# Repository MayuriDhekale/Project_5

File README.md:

# Project_5
<br>
<b>STM32F411 Multi Sensor Dashboard</b>
<br>
Moving beyond previous concepts, i have engineered this platform from clean sheet schematic to a dense, 4 layer routing solution. This custom 4-layer PCB was engineered to isolate high-frequency digital noise from the 100MHz STM32 processor, protecting the delicate micro-volt data of the MPU6050 and BMP280 sensors.

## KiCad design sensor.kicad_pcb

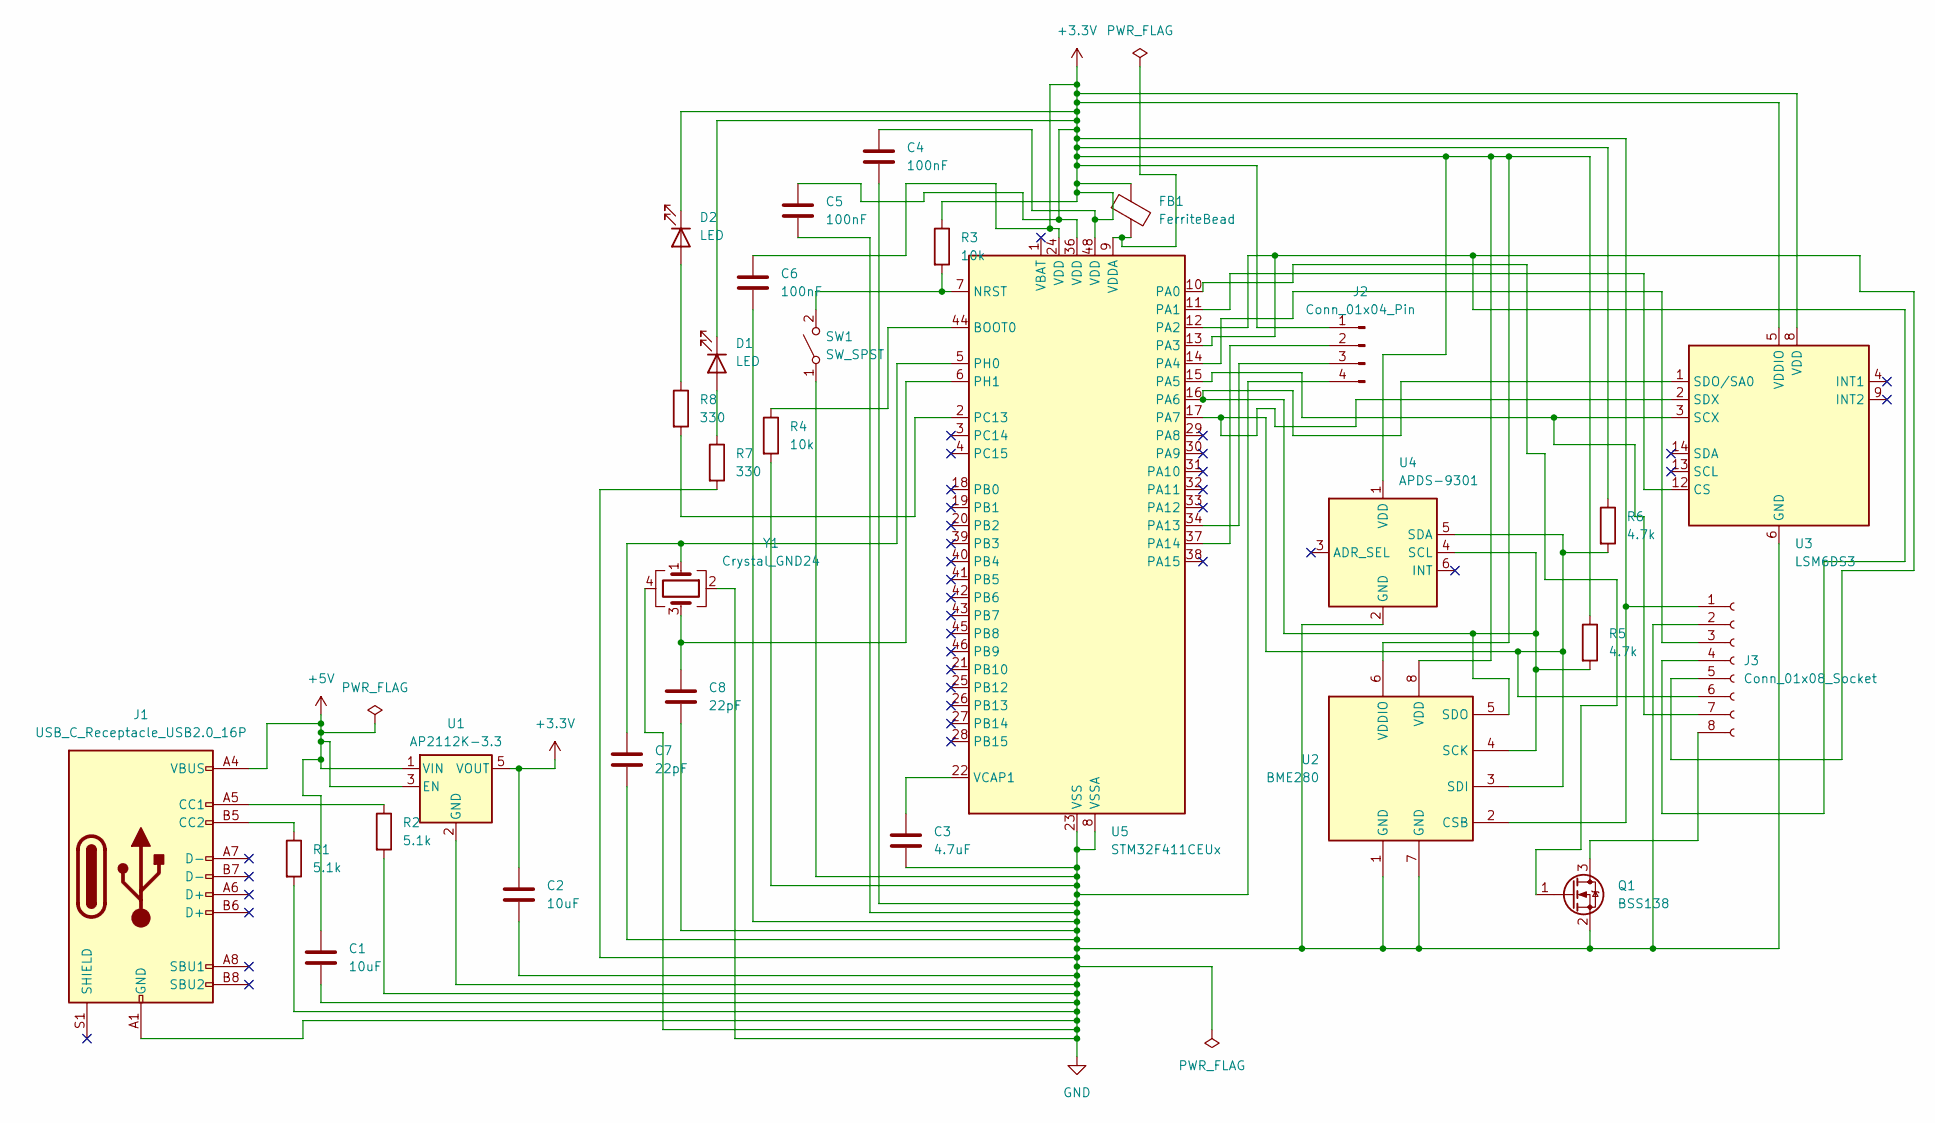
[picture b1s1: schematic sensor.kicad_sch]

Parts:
C1, C2: 10uF; C_0805_2012Metric
C3: 4.7uF; C_0603_1608Metric
C4, C5, C6: 100nF; C_0603_1608Metric
C7, C8: 22pF; C_0603_1608Metric
D1, D2: LED; LED_D5.0mm
FB1: FerriteBead; L_0603_1608Metric
J1: USB_C_Receptacle_USB2.0_16P; USB_C_Receptacle_HRO_TYPE-C-31-M-12
J2: Conn_01x04_Pin; PinHeader_1x04_P2.54mm_Vertical
J3: Conn_01x08_Socket; PinHeader_1x08_P2.54mm_Vertical
Q1: BSS138; SOT-23
R1, R2: 5.1k; R_0603_1608Metric
R3, R4: 10k; R_0603_1608Metric
R5, R6: 4.7k; R_0603_1608Metric
R7, R8: 330; R_0603_1608Metric
SW1: SW_SPST; SW_SPST_PTS645
U1: AP2112K-3.3; SOT-23-5
U2: BME280; Bosch_LGA-8_2.5x2.5mm_P0.65mm_ClockwisePinNumbering
U3: LSM6DS3; LGA-14_3x2.5mm_P0.5mm_LayoutBorder3x4y
U4: APDS-9301; Broadcom_APDS-9301
U5: STM32F411CEUx; QFN-48-1EP_7x7mm_P0.5mm_EP5.6x5.6mm
Y1: Crystal_GND24; Crystal_SMD_3225-4Pin_3.2x2.5mm

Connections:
+3.3V: C2.1, C4.1, C5.1, C6.1, D1.1 (K), D2.1 (K), FB1.1, J2.1, J3.1, R3.1, R5.1, R6.1, U1.5 (VOUT), U2.2 (CSB), U2.6 (VDDIO), U2.8 (VDD), U3.5 (VDDIO), U3.8 (VDD), U4.1 (VDD), U5.24 (VDD), U5.36 (VDD), U5.48 (VDD)
+5V: C1.1, J1.A4 (VBUS), J1.A9 (VBUS), J1.B4 (VBUS), J1.B9 (VBUS), U1.1 (VIN), U1.3 (EN)
GND: C1.2, C2.2, C3.2, C4.2, C5.2, C6.2, C7.2, C8.2, J1.A1 (GND), J1.A12 (GND), J1.B1 (GND), J1.B12 (GND), J2.4, J3.2, Q1.2 (S), R1.2, R2.2, R4.2, R7.2, SW1.1 (A), U1.2 (GND), U2.1 (GND), U2.7 (GND), U3.6 (GND), U3.7 (GND), U4.2 (GND), U5.8 (VSSA), U5.23 (VSS), U5.35 (VSS), U5.47 (VSS), U5.49 (VSS), Y1.2, Y1.4
unnamed: D1.2 (A), R7.1
unnamed: D2.2 (A), R8.1
unnamed: J1.A5 (CC1), R2.1
unnamed: J1.B5 (CC2), R1.1
unnamed: J2.2, U5.37 (PA14)
unnamed: J2.3, U5.34 (PA13)
unnamed: J3.3, U5.14 (PA4)
unnamed: J3.4, J3.5, U5.12 (PA2), U5.13 (PA3)
unnamed: J3.6, R6.2, U2.3 (SDI), U3.2 (SDX), U4.5 (SDA), U5.17 (PA7)
unnamed: J3.7, U3.3 (SCX), U5.15 (PA5)
unnamed: J3.8, Q1.3 (D)
unnamed: Q1.1 (G), U5.10 (PA0)
unnamed: R3.2, SW1.2 (B), U5.7 (NRST)
unnamed: R5.2, U2.4 (SCK), U2.5 (SDO), U3.1 (SDO/SA0), U4.4 (SCL), U5.16 (PA6)
unnamed: U3.12 (CS), U5.11 (PA1)
unnamed: R4.1, U5.44 (BOOT0)
unnamed: R8.2, U5.2 (PC13)
unnamed: C7.1, U5.5 (PH0), Y1.1
unnamed: C8.1, U5.6 (PH1), Y1.3
unnamed: C3.1, U5.22 (VCAP1)
unnamed: FB1.2, U5.9 (VDDA)

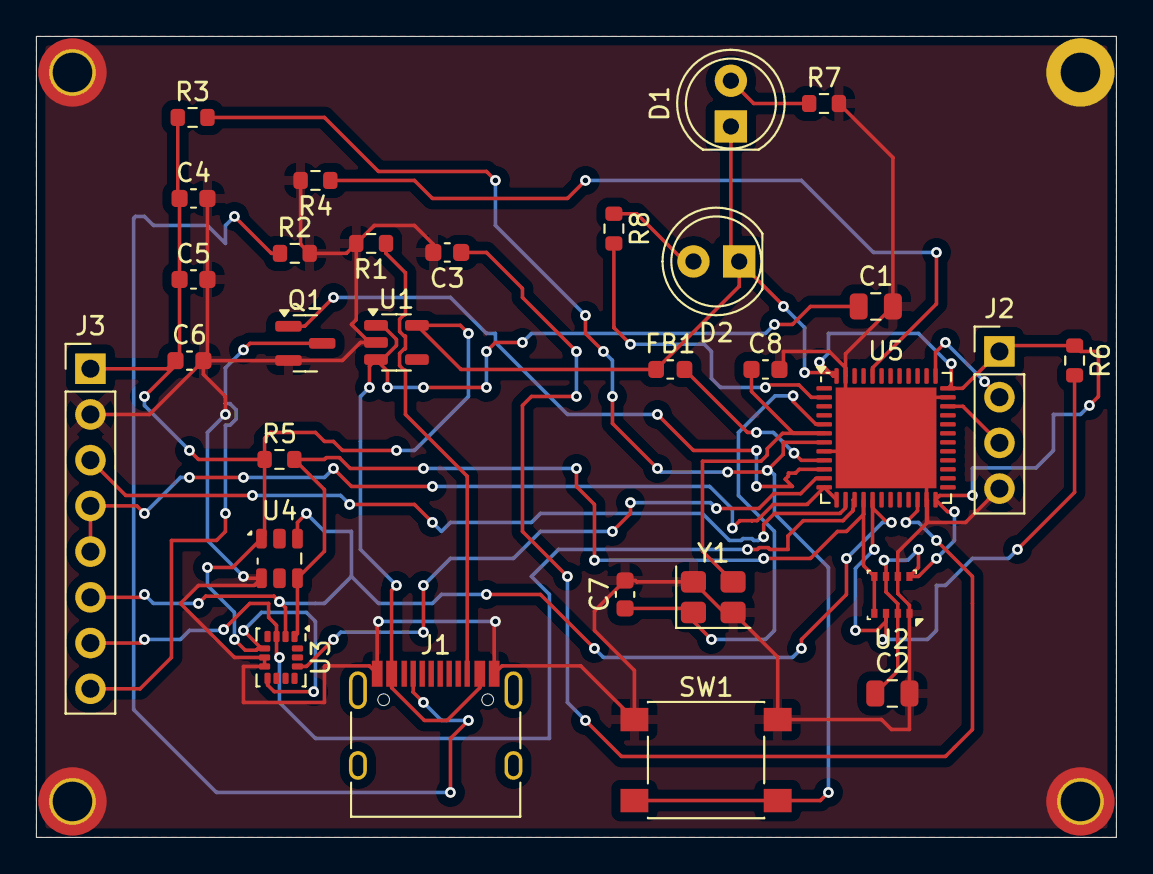
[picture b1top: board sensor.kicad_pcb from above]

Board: 4 copper layers, 60.0 x 44.5 mm, 30 parts (0 on the bottom side), 24 nets.
